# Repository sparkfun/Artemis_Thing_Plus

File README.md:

SparkFun Artemis Thing Plus
========================================

[*SparkFun Artemis Thing Plus (15574)*](https://www.sparkfun.com/products/15574)

If you are looking for a board that (almost) does it all, look no further! The SparkFun Artemis Thing Plus takes our popular Thing Plus footprint and adds in the powerful Artemis module for ultimate functionality. Fully compatible with SparkFun's Arduino core, the modern USB-C connector makes it easy to program under the Arduino IDE but for more advanced users who prefer to use the power and speed of professional tools, we've also exposed the JTAG connector. To make the Thing Plus even easier to use, we've moved a few pins around to make the board Feather compatible and it utilizes our handy Qwiic Connect System which means no soldering or shields are required to connect it to the rest of your system!

With 1MB flash and 384k RAM you'll have plenty of room for your sketches. The on-board Artemis module runs at 48MHz with a 96MHz turbo mode available and with Bluetooth to boot! We've added a digital MEMS microphone for folks wanting to experiment with always-on voice commands with TensorFlow and machine learning. The addition of the Qwiic connector opens up plug-and-play I<sup>2</sup>C functionality with our wide array of Qwiic boards. 

With so much functionality, the SparkFun Artemis Thing Plus is an ideal choice for your Internet of Things project. We've even made it Feather-compatible so you can take advantage of a shield option in case you didn't want to use our Qwiic Connect System! If you need more Apollo3 functionality or a more concise form factor, check out our Artemis ATP or Artemis Nano.

Repository Contents
-------------------

* **/Hardware** - Eagle design files (.brd, .sch)

Documentation
--------------
* **[Hookup Guide](https://learn.sparkfun.com/tutorials/hookup-guide-for-the-sparkfun-artemis-thing-plus)** - Basic hookup guide for the Artemis Thing Plus.
* **[Artemis Development with Arduino](https://learn.sparkfun.com/tutorials/artemis-development-with-arduino)**
* **[Ambiq Apollo3 SDK SetUp](https://learn.sparkfun.com/tutorials/using-sparkfun-edge-board-with-ambiq-apollo3-sdk)**
* **[Designing with the SparkFun Artemis](https://learn.sparkfun.com/tutorials/designing-with-the-sparkfun-artemis)**
* **[CH340E USB to serial IC Drivers](https://www.sparkfun.com/ch340)**
* **[SparkFun Fritzing repo](https://github.com/sparkfun/Fritzing_Parts)** - Fritzing diagrams for SparkFun products.

License Information
-------------------

This product is _**open source**_! 

Please review the LICENSE.md file for license information. 

If you have any questions or concerns on licensing, please contact technical support on our [SparkFun forums](https://forum.sparkfun.com/viewforum.php?f=152).

Distributed as-is; no warranty is given.

- Your friends at SparkFun.

_<COLLABORATION CREDIT>_

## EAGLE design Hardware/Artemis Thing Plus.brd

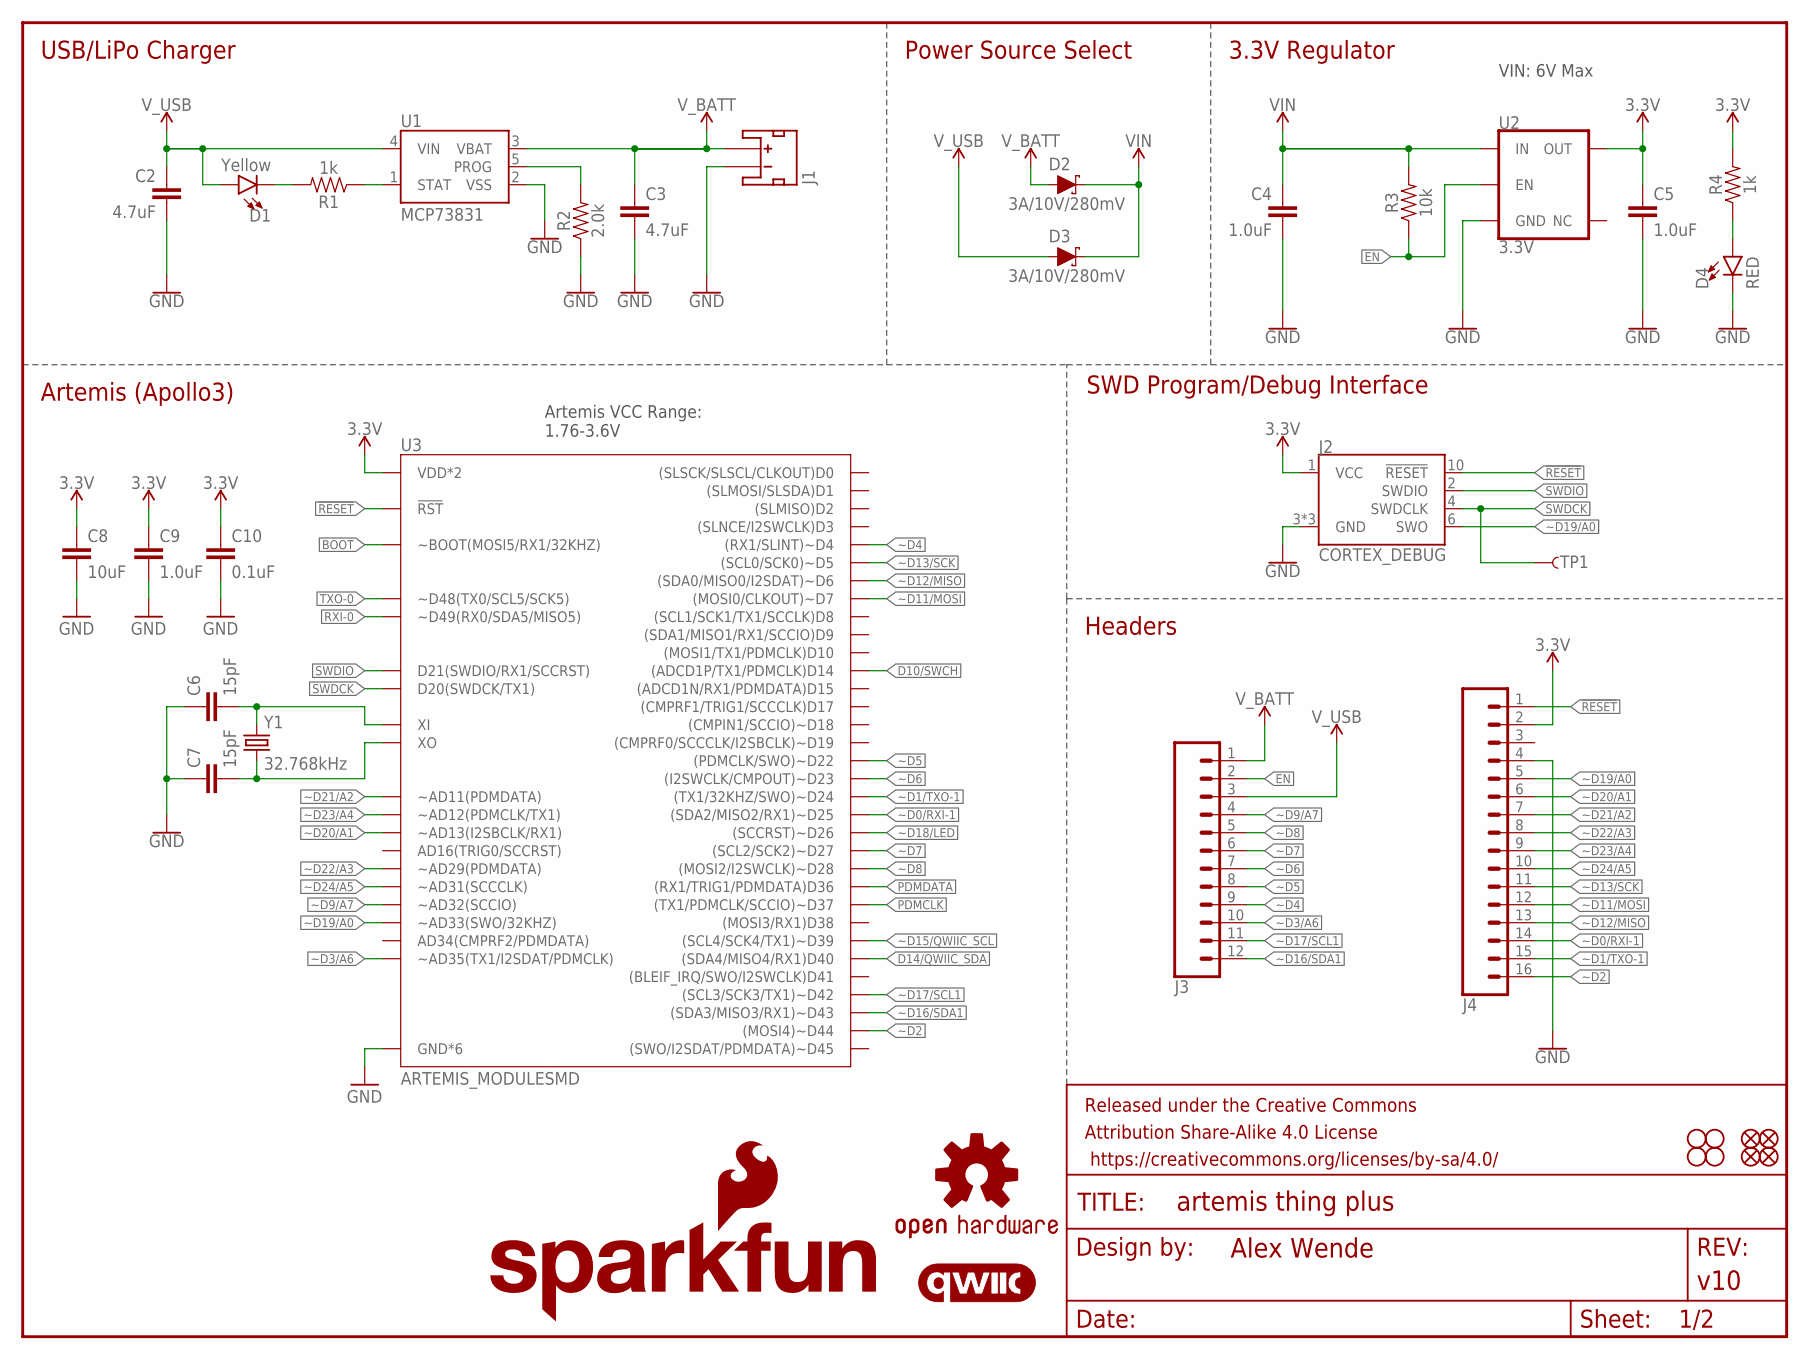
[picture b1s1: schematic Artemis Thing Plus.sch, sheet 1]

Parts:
C2, C3: 4.7uF; 0603
C4, C5: 1.0uF; 0402-TIGHT
C6, C7: 15pF; 0603
C8: 10uF; 0603
C9: 1.0uF; 0603
C10: 0.1uF; 0603
D1: Yellow; LED-0603
D2, D3: 3A/10V/280mV; SOD-323
D4: RED; LED-0603
FD1, FD2, FD3, FD4: FIDUCIALUFIDUCIAL; FIDUCIAL-MICRO
FRAME1: FRAME-LETTER; CREATIVE_COMMONS
H1, H2, H3, H4: STAND-OFF
J1: JST_2MM_MALE; JST-2-SMD
J2: CORTEX_DEBUG; 2X5-PTH-1.27MM-NO_SILK
J3: CONN_12SM_SQ_NO_SILK; 1X12_SM_SQ_NOSILK
J4: CONN_161X16_SM_SQ_NOSILK; 1X16_SM_SQ_NOSILK
LOGO1: OSHW-LOGOS; OSHW-LOGO-S
LOGO2: QWIIC_LOGO_5MM; QWIIC_5MM
LOGO3: SFE_LOGO_NAME_FLAME.1_INCH; SFE_LOGO_NAME_FLAME_.1
R1, R4: 1k; 0603
R2: 2.0k; 0603
R3: 10k; 0603
TP1: TEST-POINTTP_15TH_THRU; TP_15TH
U1: MCP73831; SOT23-5
U2: 3.3V; SOT23-5
U3: ARTEMIS_MODULESMD; ARTEMIS_FP
Y1: 32.768kHz; CRYSTAL-SMD-3.2X1.5MM

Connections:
3.3V: C5.1, C8.1, C9.1, C10.1, J2.1 (VCC), J4.2, R4.2, U2.5 (OUT), U3.VDD@36 (VDD*2), U3.VDD@37 (VDD*2); also elsewhere on the board
!RESET: J2.10 (!RESET), J4.1, U3.~RST (!RST); also elsewhere on the board
BOOT: U3.BOOT (~BOOT(MOSI5/RX1/32KHZ)); also elsewhere on the board
D10/SWCH: U3.D14 ((ADCD1P/TX1/PDMCLK)D14); also elsewhere on the board
D14/QWIIC_SDA: U3.D40 ((SDA4/MISO4/RX1)D40); also elsewhere on the board
EN: J3.2, R3.1, U2.3 (EN)
GND: C2.2, C3.2, C4.2, C5.2, C6.1, C7.1, C8.2, C9.2, C10.2, D4.C, J1.1 (-), J2.3 (GND), J2.5 (GND), J2.9 (GND), J4.4, R2.1, U1.2 (VSS), U2.2 (GND), U3.GND@1 (GND*6), U3.GND@22 (GND*6), U3.GND@38 (GND*6), U3.GND@39 (GND*6), U3.GND@47 (GND*6), U3.GND@59 (GND*6); also elsewhere on the board
unnamed: R2.2, U1.5 (PROG)
unnamed: C7.2, U3.XO, Y1.P$2 (2)
unnamed: D1.C, R1.2
unnamed: R1.1, U1.1 (STAT)
unnamed: C6.2, U3.XI, Y1.P$1 (1)
unnamed: D4.A, R4.1
PDMCLK: U3.~D37 ((TX1/PDMCLK/SCCIO)~D37); also elsewhere on the board
PDMDATA: U3.D36 ((RX1/TRIG1/PDMDATA)D36); also elsewhere on the board
RXI-0: U3.RXI-0 (~D49(RX0/SDA5/MISO5)); also elsewhere on the board
SWDCK: J2.4 (SWDCLK), TP1.P$1, U3.SWDCK (D20(SWDCK/TX1))
SWDIO: J2.2 (SWDIO), U3.SWDIO (D21(SWDIO/RX1/SCCRST))
TXO-0: U3.TXO-0 (~D48(TX0/SCL5/SCK5)); also elsewhere on the board
VIN: C4.1, D2.C, D3.C, R3.2, U2.1 (IN)
V_BATT: C3.1, D2.A, J1.2 (+), J3.1, U1.3 (VBAT)
V_USB: C2.1, D1.A, D3.A, J3.3, U1.4 (VIN); also elsewhere on the board
~D0/RXI-1: J4.14, U3.~D25 ((SDA2/MISO2/RX1)~D25)
~D1/TXO-1: J4.15, U3.~D24 ((TX1/32KHZ/SWO)~D24)
~D2: J4.16, U3.~D44 ((MOSI4)~D44)
~D3/A6: J3.10, U3.~AD35 (~AD35(TX1/I2SDAT/PDMCLK))
~D4: J3.9, U3.~D4 ((RX1/SLINT)~D4)
~D5: J3.8, U3.~D22 ((PDMCLK/SWO)~D22)
~D6: J3.7, U3.~D23 ((I2SWCLK/CMPOUT)~D23)
~D7: J3.6, U3.~D27 ((SCL2/SCK2)~D27)
~D8: J3.5, U3.~D28 ((MOSI2/I2SWCLK)~D28)
~D9/A7: J3.4, U3.~AD32 (~AD32(SCCIO))
~D11/MOSI: J4.12, U3.D7 ((MOSI0/CLKOUT)~D7)
~D12/MISO: J4.13, U3.~D6 ((SDA0/MISO0/I2SDAT)~D6)
~D13/SCK: J4.11, U3.~D5 ((SCL0/SCK0)~D5)
~D15/QWIIC_SCL: U3.~D39 ((SCL4/SCK4/TX1)~D39); also elsewhere on the board
~D16/SDA1: J3.12, U3.~D43 ((SDA3/MISO3/RX1)~D43)
~D17/SCL1: J3.11, U3.~D42 ((SCL3/SCK3/TX1)~D42)
~D18/LED: U3.~D26 ((SCCRST)~D26); also elsewhere on the board
~D19/A0: J2.6 (SWO), J4.5, U3.~AD33/SWO (~AD33(SWO/32KHZ))
~D20/A1: J4.6, U3.~AD13 (~AD13(I2SBCLK/RX1))
~D21/A2: J4.7, U3.~AD11 (~AD11(PDMDATA))
~D22/A3: J4.8, U3.~AD29 (~AD29(PDMDATA))
~D23/A4: J4.9, U3.~AD12 (~AD12(PDMCLK/TX1))
~D24/A5: J4.10, U3.~AD31 (~AD31(SCCCLK))

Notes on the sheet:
SWD Program/Debug Interface
Headers
Artemis (Apollo3)
USB/LiPo Charger
Power Source Select
3.3V Regulator
Artemis VCC Range: 1.76-3.6V
VIN: 6V Max

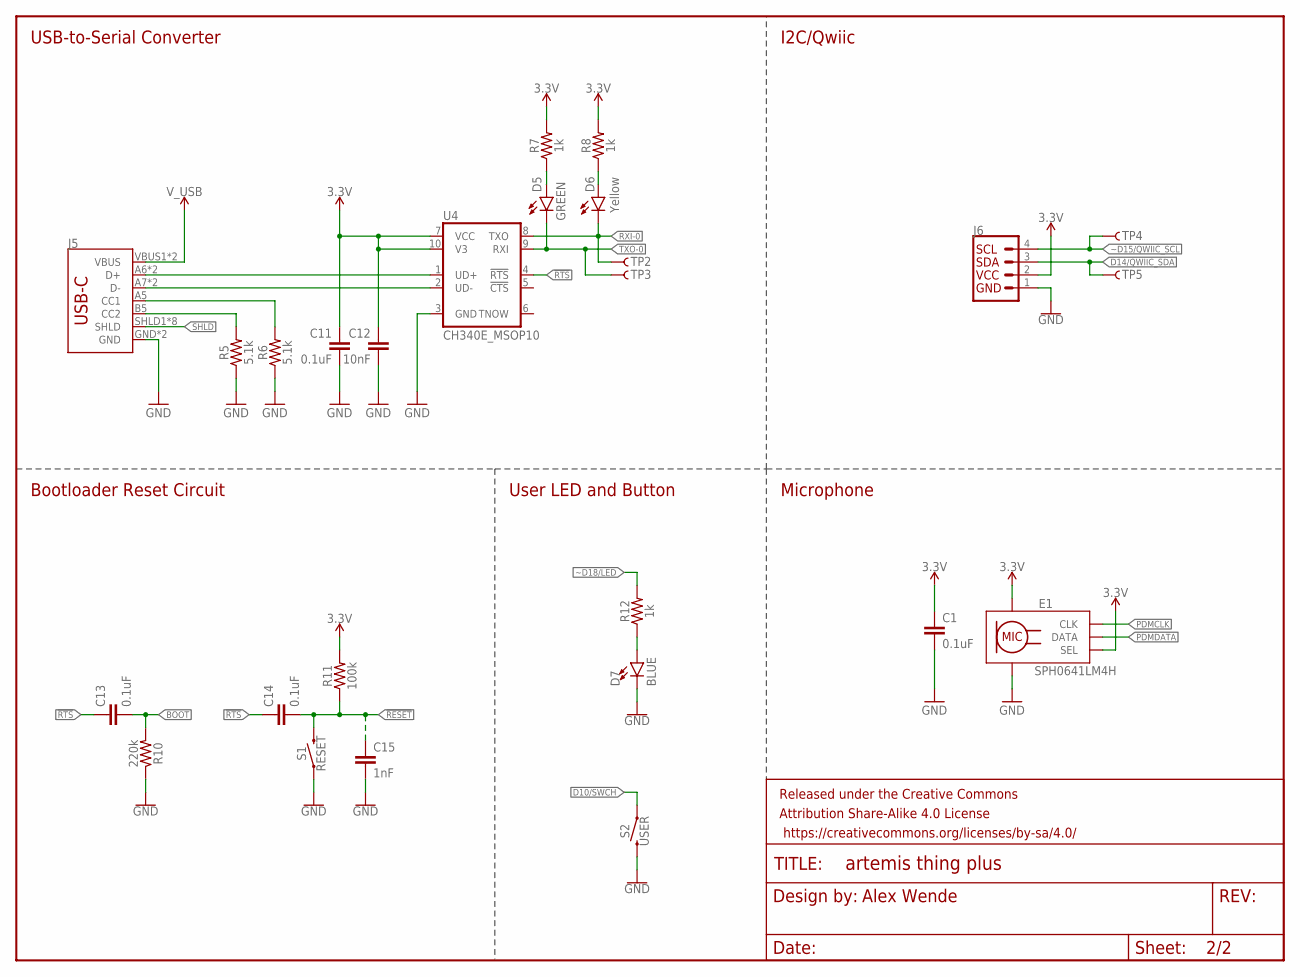
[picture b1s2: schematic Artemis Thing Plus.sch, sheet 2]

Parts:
C1: 0.1uF; 0402-TIGHT
C11, C13, C14: 0.1uF; 0603
C12: 10nF; 0603
C15: 1nF; 0603
D5: GREEN; LED-0603
D6: Yellow; LED-0603
D7: BLUE; LED-0603
E1: SPH0641LM4H; SPH0641LM4H-1_MICROPHONE
FRAME2: FRAME-LETTERNO_PACKAGE; DUMMY
J5: USB-C; USB-C-16P
J6: QWIIC_CONNECTORJS-1MM; JST04_1MM_RA
R5, R6: 5.1k; 0603
R7, R8, R12: 1k; 0603
R10: 220k; 0603
R11: 100k; 0603
S1: RESET; TACTILE_SWITCH_SMD_4.6X2.8MM
S2: USER; TACTILE_SWITCH_SMD_4.6X2.8MM
TP2, TP3, TP4, TP5: TEST-POINTTP_15TH_THRU; TP_15TH
U4: CH340E_MSOP10; MSOP10

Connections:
3.3V: C1.1, C11.1, C12.1, E1.2 (SEL), E1.5 (VDD), J6.2, R7.2, R8.2, R11.2, U4.7 (VCC), U4.10 (V3); also elsewhere on the board
!RESET: C14.2, C15.1, R11.1, S1.3 (2), S1.4 (2); also elsewhere on the board
!RTS: C13.1, C14.1, U4.4 (!RTS)
BOOT: C13.2, R10.2; also elsewhere on the board
CC1: J5.A5 (CC1), R6.2
CC2: J5.B5 (CC2), R5.2
D10/SWCH: S2.1, S2.2 (1); also elsewhere on the board
D14/QWIIC_SDA: J6.3, TP5.P$1; also elsewhere on the board
D+1: J5.A6 (D+), J5.B6 (D+), U4.1 (UD+)
D-1: J5.A7 (D-), J5.B7 (D-), U4.2 (UD-)
GND: C1.2, C11.2, C12.2, C15.2, D7.C, E1.3 (GND), E1.6 (GND), E1.7 (GND), E1.8 (GND), J5.GND, J5.GND2 (GND), J6.1, R5.1, R6.1, R10.1, S1.1, S1.2 (1), S2.3 (2), S2.4 (2), U4.3 (GND); also elsewhere on the board
unnamed: D5.A, R7.1
unnamed: D7.A, R12.1
unnamed: D6.A, R8.1
PDMCLK: E1.4 (CLK); also elsewhere on the board
PDMDATA: E1.1 (DATA); also elsewhere on the board
RXI-0: D6.C, TP2.P$1, U4.8 (TXO); also elsewhere on the board
SHLD: J5.SHLD1 (SHLD), J5.SHLD2 (SHLD), J5.SHLD3 (SHLD), J5.SHLD4 (SHLD), J5.SHLD5 (SHLD), J5.SHLD6 (SHLD), J5.SHLD7 (SHLD), J5.SHLD8 (SHLD)
TXO-0: D5.C, TP3.P$1, U4.9 (RXI); also elsewhere on the board
V_USB: J5.VBUS1 (VBUS), J5.VBUS2 (VBUS); also elsewhere on the board
~D15/QWIIC_SCL: J6.4, TP4.P$1; also elsewhere on the board
~D18/LED: R12.2; also elsewhere on the board

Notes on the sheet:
Microphone
USB-to-Serial Converter
Bootloader Reset Circuit
User LED and Button
I2C/Qwiic
Alex Wende

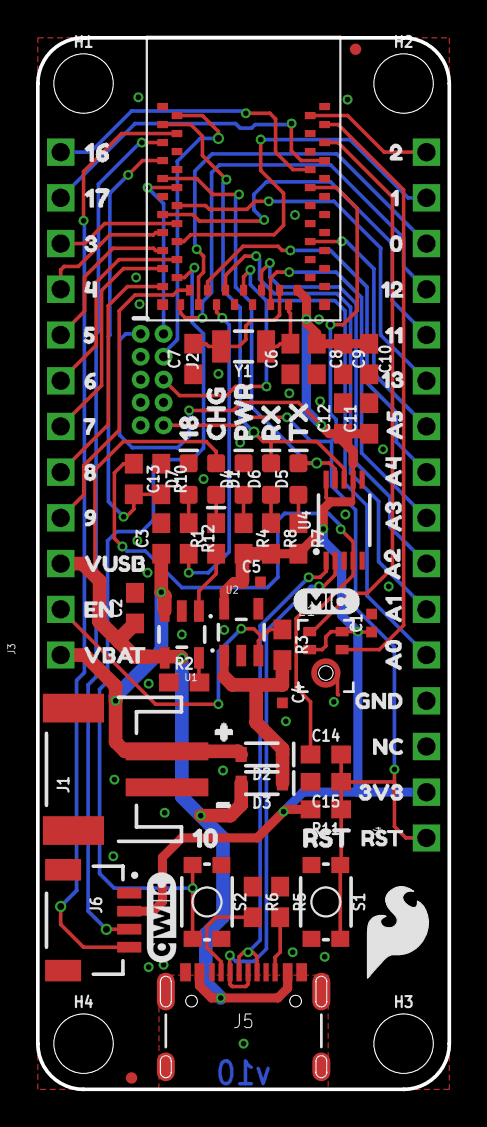
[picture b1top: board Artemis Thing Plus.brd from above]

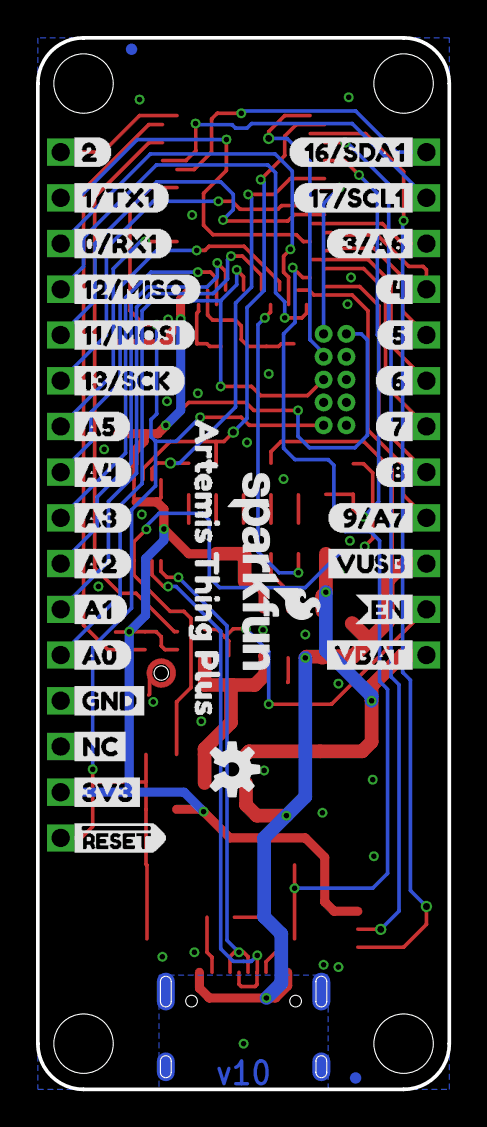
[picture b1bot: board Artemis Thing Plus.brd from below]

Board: 2 copper layers, 22.9 x 58.4 mm, 133 parts (33 on the bottom side), 54 nets.

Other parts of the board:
U$1: 160
U$2: 171
U$3: 32
U$4: 43
U$5: 54
U$6: 65
U$7: 76
U$8: 87
U$9: 98
U$10: VUSB9
U$11: EN10
U$12: VBAT11
U$13: 227
U$14: 126
U$15: 025
U$16: 1123
U$17: 1224
U$18: 1322
U$19: A521
U$20: A420
U$21: A319
U$22: A218
U$23: A117
U$24: A016
U$25: GND13
U$26: NC12
U$27, U$48: 3V314
U$28: RST15
U$29: 184
U$30: CHG1
U$31: PWR2
U$32: RX3
U$33: TX4
U$34: 20
U$35: 1#TX11
U$36: 0#RX12
U$37: 12#MISO3
U$38: 11#MOSI4
U$39: 13#SCK5
U$40: A56
U$41: A47
U$42: A38
U$43: A29
U$44: A110
U$45: A011
U$46: GND12
U$47: NC13
U$49: #RESET15
U$50: 16#SDA12
U$51: 17#SCL13
U$52: 412
U$53: 513
U$54: 614
U$55: 715
U$56: 816
U$57: 9#A719
U$58: 3#A60
U$59: VUSB25
U$60: EN26
U$61: VBAT27
U$62: 100
U$63: RST1
U$64: ARTEMIS_THING_PLUS0
U$65: SFE_LOGO_FLAME_.2
U$66: MIC0
U$67: #0
U$68: #1

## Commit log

2019-07-29 v10
    Initial Commit
2019-08-05 v10 Update
    Schematic:
    - Change 100k pull-down resistor in bootloader circuit to DNP
    - Replaced diodes with lower forward voltage drop
    - Added second I2C Bus to breakout pins. All broken out pins are now PWM capable
    - Replaced 4.7k LEDs resistors to 1k for all LEDs
    - Added testpoints for Qwiic data lines
2019-08-06 v10 design review changes
2019-08-07 v10 QC fixes
    Added + and - symbols to JST connector
2019-08-28 Update Artemis Thing Plus.brd
    Adjusted CH340 RTS signal for better ground pour

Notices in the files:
parts and their libraries:
SparkFun-Capacitors: Licensing: Creative Commons ShareAlike 4.0 International - https://creativecommons.org/licenses/by-sa/4.0
SparkFun-Aesthetics: Released under the Creative Commons Attribution Share-Alike 4.0 License
SparkFun-Aesthetics: https://creativecommons.org/licenses/by-sa/4.0
